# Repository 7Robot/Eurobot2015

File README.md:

# Eurobot2015

     ______  _____      _           _
    |___   /| ___ \    | |         | |
        / / | |_/ /___ | |__   ___ | |_
       / /  |    // _ \|  _ \ / _ \|  _|
      / /   | |\ \ (_) | |_) | (_) | |_
     /_/    |_| \_\___/|____/ \___/ \__|
                              7robot.fr

Gathering repository for the 2015 Robotics French Cup code.

Note : RP7 -> uart2

* Tarantibot

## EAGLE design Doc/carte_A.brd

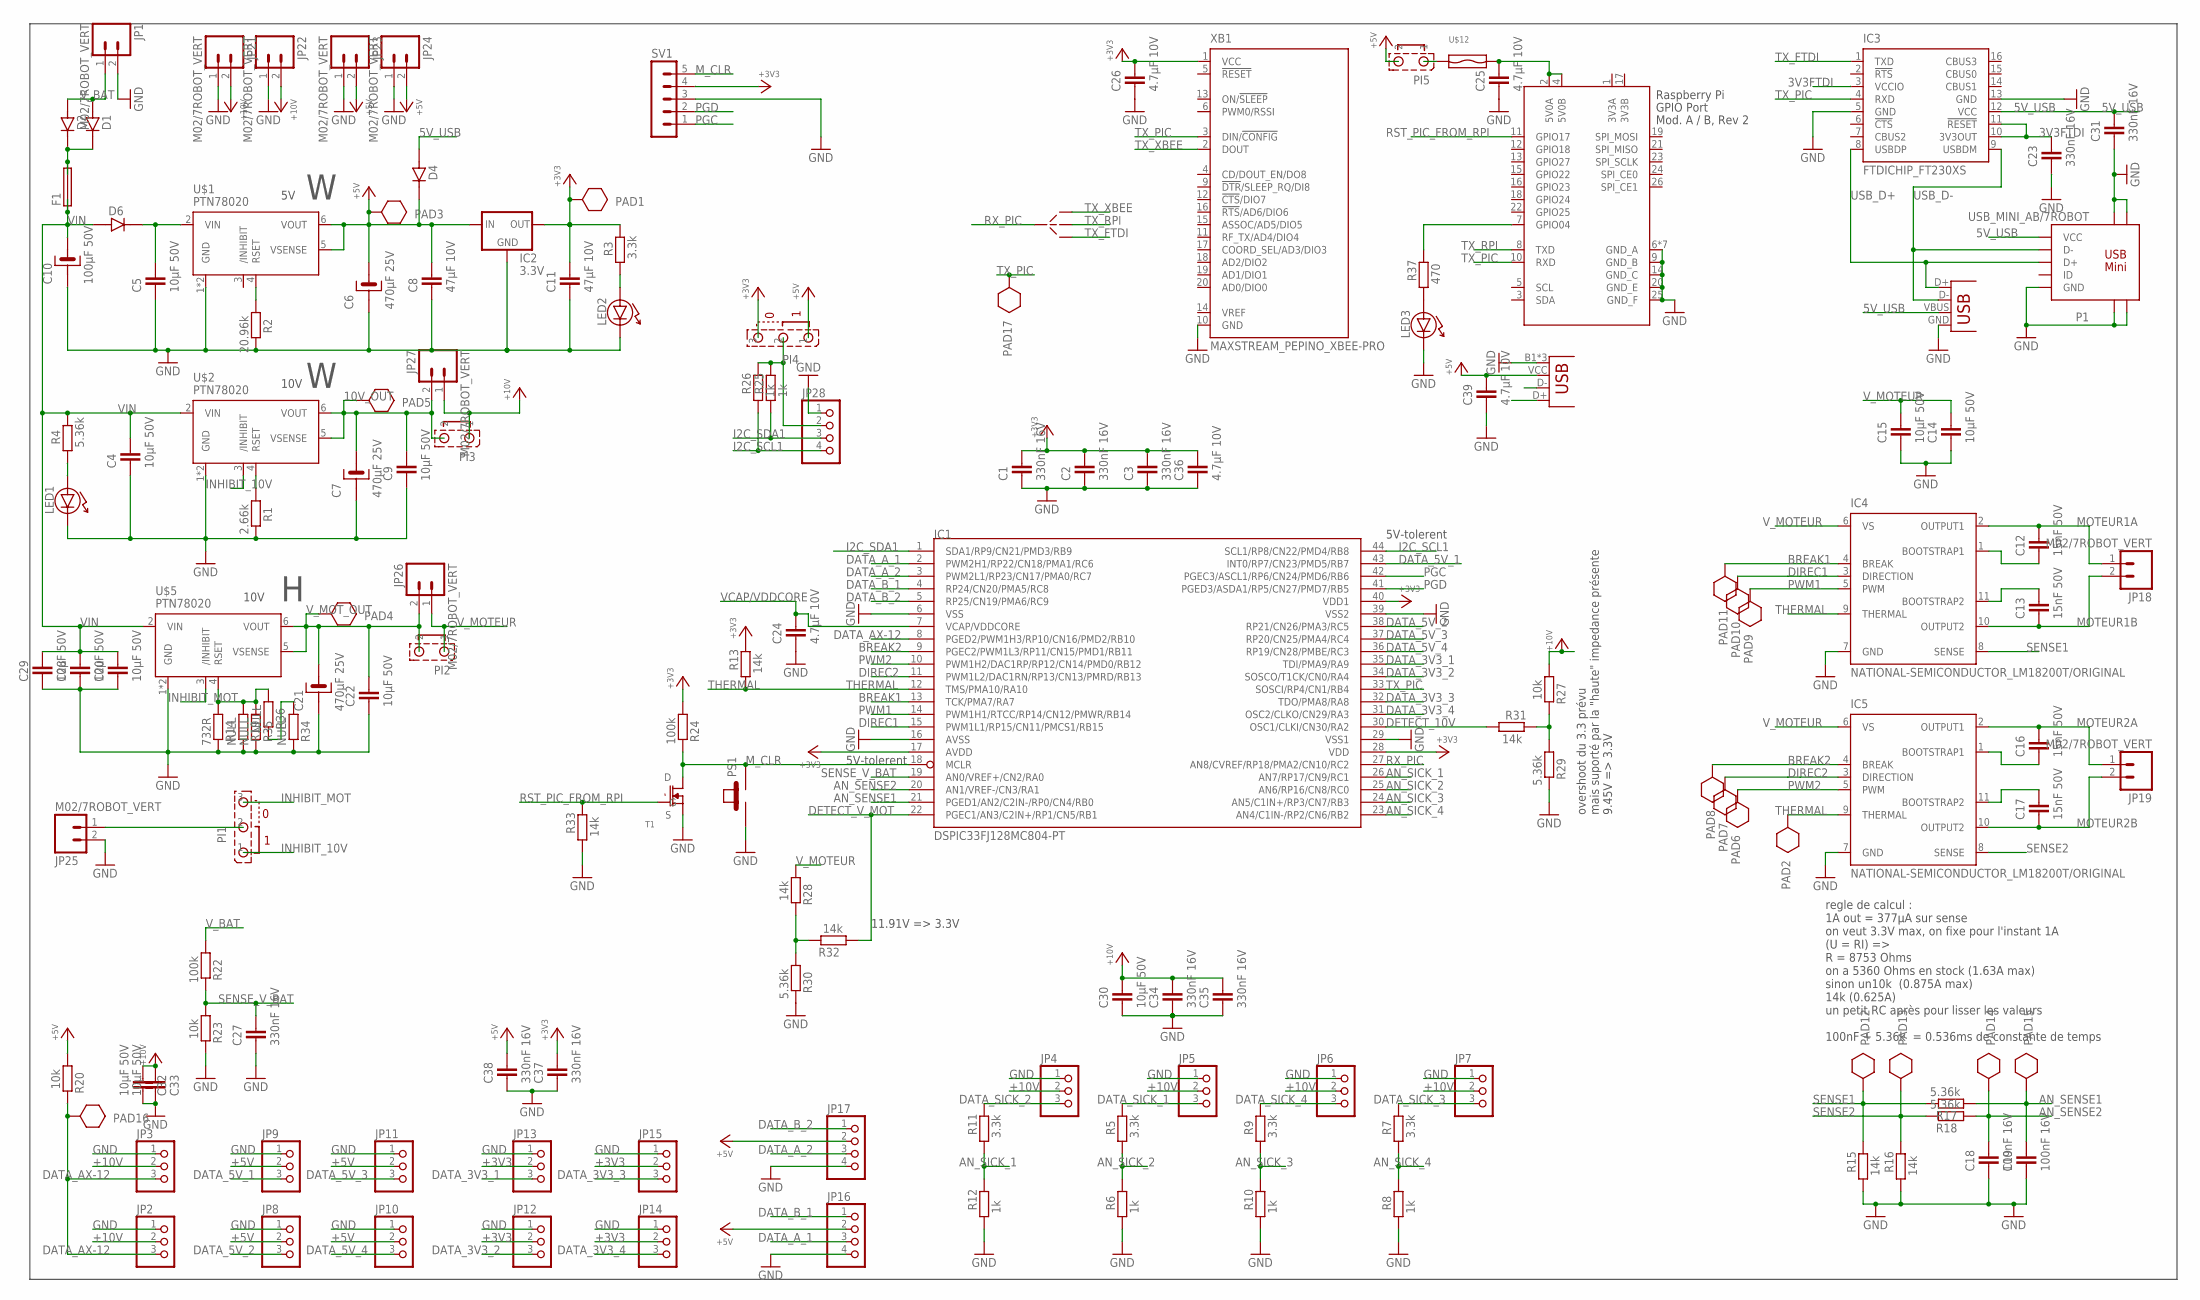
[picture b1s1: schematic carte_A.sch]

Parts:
C1, C2, C3, C23, C27, C31, C34, C35, C37, C38: 330nF 16V; 0805
C4, C5, C9, C14, C15, C20, C22, C28, C29, C30, C32, C33: 10µF 50V; 1206
C6, C7, C21: 470µF 25V; CHIM8P3.5
C8, C11: 47µF 10V; 1210
C10: 100µF 50V; CHIM8P3.5
C12, C13, C16, C17: 15nF 50V; 0805
C18, C19: 100nF 16V; 0805
C24, C25, C26, C36, C39: 4.7µF 10V; 0805
D1, D2, D4, D6: DIODES_DIODE/DO41; DIODES_DO41
F1: PORTE_FUSIBLE; SHK20L
IC1: DSPIC33FJ128MC804-PT; TQFP44
IC2: 3.3V; V-REG_78XXS
IC3: FTDICHIP_FT230XS; FTDICHIP_SSOP16
IC4, IC5: NATIONAL-SEMICONDUCTOR_LM18200T/ORIGINAL; NATIONAL-SEMICONDUCTOR_TO-220-11
JP1, JP18, JP19, JP21, JP22, JP23, JP24, JP25, JP26, JP27: M02/7ROBOT_VERT; CONN_5MM
JP2, JP3, JP4, JP5, JP6, JP7, JP8, JP9, JP10, JP11, JP12, JP13, JP14, JP15: PINHD-1X3; 1X03
JP16, JP17, JP28: PINHD-1X4; 1X04
JP20: USB-B; SPARKFUN-CONNECTORS_USB-B-PTH
JP29: USB/VERT; USB-A-FEMALE_VERTICAL
LED1, LED2: OPTO_OSC_LED/5MM; OPTO_OSC_LED5
LED3: LED/1206; LED1206
P1: USB_MINI_AB/7ROBOT; USB_MINI_AB_7ROBOT
PAD1, PAD3, PAD4, PAD5, PAD17: STRAP_PAD/CMS2; STRAP_PAD_CMS_2
PAD2, PAD6, PAD7, PAD8, PAD9, PAD10, PAD11, PAD12, PAD13, PAD14, PAD15, PAD16: STRAP_PAD/CMS1_5; STRAP_PAD_CMS_1_5
PI1, PI4: STCMS_3/CMS; STCMS_3
PI2, PI3, PI5: STCMS_2
PS1: ELECTROMECA_PEPINO_POUSSOIR/D_MINI; ELECTROMECA_PEPINO_B3F
R1: 2.66k; 0805
R2: 20.96k; 0805
R3, R5, R7, R9, R11: 3.3k; 0805
R4, R17, R18, R29, R30: 5.36k; 0805
R6, R8, R10, R12, R25, R26: 1k; 0805
R13, R15, R16, R28, R31, R32, R33: 14k; 0805
R14: 732R; 0805
R19, R34, R35, R36: NULL; 0805
R20, R23, R27: 10k; 1206
R22, R24: 100k; 1206
R37: 470; 0805
SV1: CON-LSTB_MA05-1
T1: MOS_N/SOT23; SOT23
U$1, U$2, U$5: PTN78020
U$9: STCMS_4
U$12: FUSE_REARMABLE/1206; 1206
X1: RASPI_BOARD_B-#_E6P; RASPI_BOARD_AB-_EDGES_6DRILL_PAD
XB1: MAXSTREAM_PEPINO_XBEE-PRO

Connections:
3V3A: X1.1 (3V3A)
3V3B: X1.17 (3V3B)
3V3FTDI: C23.1, IC3.3 (VCCIO), IC3.10 (3V3OUT), IC3.11 (!RESET)
5V_RPI: C25.1, U$12.2, X1.2 (5V0A), X1.4 (5V0B)
5V_USB: C31.1, D4.A, IC3.12 (VCC), JP20.VBUS, P1.1 (VCC)
10V_OUT: C7.P, C9.1, JP27.2, PAD5.P$1, PI3.2, U$2.5 (VSENSE), U$2.6 (VOUT)
+3V3: C1.1, C2.1, C3.1, C11.1, C26.1, C36.1, C37.1, IC1.17 (AVDD), IC1.28 (VDD), IC1.40 (VDD1), IC2.OUT, JP12.2, JP13.2, JP14.2, JP15.2, PAD1.P$1, PI4.3, R3.2, R13.2, R24.1, SV1.4, XB1.1 (VCC)
+5V: C6.P, C8.1, C38.1, C39.1, D4.K, IC2.IN, JP8.2, JP9.2, JP10.2, JP11.2, JP16.2, JP17.2, JP23.2, JP24.2, JP29.VCC (VBUS), PAD3.P$1, PI4.1, PI5.2, R20.1, U$1.5 (VSENSE), U$1.6 (VOUT)
+10V: C30.1, C32.1, C33.1, C34.1, C35.1, JP2.2, JP3.2, JP4.2, JP5.2, JP6.2, JP7.2, JP21.2, JP22.2, JP27.1, PI3.1, R27.1
AN_SENSE1: C19.1, IC1.21 (PGED1/AN2/C2IN-/RP0/CN4/RB0), PAD15.P$1, R17.1
AN_SENSE2: C18.1, IC1.20 (AN1/VREF-/CN3/RA1), PAD14.P$1, R18.1
AN_SICK_1: IC1.26 (AN7/RP17/CN9/RC1), R11.1, R12.2
AN_SICK_2: IC1.25 (AN6/RP16/CN8/RC0), R5.1, R6.2
AN_SICK_3: IC1.24 (AN5/C1IN+/RP3/CN7/RB3), R9.1, R10.2
AN_SICK_4: IC1.23 (AN4/C1IN-/RP2/CN6/RB2), R7.1, R8.2
BREAK1: IC1.13 (TCK/PMA7/RA7), IC4.4 (BREAK), PAD11.P$1
BREAK2: IC1.9 (PGEC2/PWM1L3/RP11/CN15/PMD1/RB11), IC5.4 (BREAK), PAD8.P$1
DATA_3V3_1: IC1.35 (TDI/PMA9/RA9), JP13.3
DATA_3V3_2: IC1.34 (SOSCO/T1CK/CN0/RA4), JP12.3
DATA_3V3_3: IC1.32 (TDO/PMA8/RA8), JP15.3
DATA_3V3_4: IC1.31 (OSC2/CLKO/CN29/RA3), JP14.3
DATA_5V_1: IC1.43 (INT0/RP7/CN23/PMD5/RB7), JP9.3
DATA_5V_2: IC1.38 (RP21/CN26/PMA3/RC5), JP8.3
DATA_5V_3: IC1.37 (RP20/CN25/PMA4/RC4), JP11.3
DATA_5V_4: IC1.36 (RP19/CN28/PMBE/RC3), JP10.3
DATA_AX-12: IC1.8 (PGED2/PWM1H3/RP10/CN16/PMD2/RB10), JP2.3, JP3.3, PAD16.P$1, R20.2
DATA_A_1: IC1.2 (PWM2H1/RP22/CN18/PMA1/RC6), JP16.3
DATA_A_2: IC1.3 (PWM2L1/RP23/CN17/PMA0/RC7), JP17.3
DATA_B_1: IC1.4 (RP24/CN20/PMA5/RC8), JP16.1
DATA_B_2: IC1.5 (RP25/CN19/PMA6/RC9), JP17.1
DATA_SICK_1: JP5.3, R5.2
DATA_SICK_2: JP4.3, R11.2
DATA_SICK_3: JP7.3, R7.2
DATA_SICK_4: JP6.3, R9.2
DETECT_10V: IC1.30 (OSC1/CLKI/CN30/RA2), R31.1
DETECT_V_MOT: IC1.22 (PGEC1/AN3/C2IN+/RP1/CN5/RB1), R32.1
DIREC1: IC1.15 (PWM1L1/RP15/CN11/PMCS1/RB15), IC4.3 (DIRECTION), PAD10.P$1
DIREC2: IC1.11 (PWM1L2/DAC1RN/RP13/CN13/PMRD/RB13), IC5.3 (DIRECTION), PAD7.P$1
GND: C1.2, C2.2, C3.2, C4.2, C5.2, C6.N, C7.N, C8.2, C9.2, C10.N, C11.2, C14.2, C15.2, C18.2, C19.2, C20.2, C21.N, C22.2, C23.2, C24.2, C25.2, C26.2, C27.2, C28.2, C29.2, C30.2, C31.2, C32.2, C33.2, C34.2, C35.2, C36.2, C37.2, C38.2, C39.2, IC1.6 (VSS), IC1.16 (AVSS), IC1.29 (VSS1), IC1.39 (VSS2), IC2.GND, IC3.5 (GND), IC3.13 (GND), IC4.7 (GND), IC5.7 (GND), JP1.2, JP2.1, JP3.1, JP4.1, JP5.1, JP6.1, JP7.1, JP8.1, JP9.1, JP10.1, JP11.1, JP12.1, JP13.1, JP14.1, JP15.1, JP16.4, JP17.4, JP20.GND, JP21.1, JP22.1, JP23.1, JP24.1, JP25.2, JP28.1, JP29.B1 (GND), JP29.B2 (GND), JP29.GND, LED1.K, LED2.K, LED3.K, P1.5 (GND), P1.SH@1 (PT1), P1.SH@2 (PT2), P1.SH@3 (PT3), P1.SH@4 (PT4), PS1.1, R1.2, R2.2, R6.1, R8.1, R10.1, R12.1, R14.2, R15.1, R16.1, R19.2, R23.2, R29.2, R30.2, R33.1, R34.2, R35.2, SV1.3, T1.2 (S), U$1.1 (GND), U$1.7 (GND), U$2.1 (GND), U$2.7 (GND), U$5.1 (GND), U$5.7 (GND), X1.6 (GND_A), X1.9 (GND_B), X1.14 (GND_C), X1.20 (GND_E), X1.25 (GND_F), X1.41 (GND_A), X1.42 (GND_A), X1.43 (GND_A), X1.44 (GND_A), X1.45 (GND_A), X1.46 (GND_A), XB1.10 (GND)
I2C_SCL1: IC1.44 (SCL1/RP8/CN22/PMD4/RB8), JP28.4, R26.1
I2C_SDA1: IC1.1 (SDA1/RP9/CN21/PMD3/RB9), JP28.3, R25.1
INHIBIT_10V: PI1.1, U$2.3 (/INHIBIT)
INHIBIT_MOT: PI1.3, U$5.3 (/INHIBIT)
MOTEUR1A: C12.1, IC4.2 (OUTPUT1), JP18.1
MOTEUR1B: C13.2, IC4.10 (OUTPUT2), JP18.2
MOTEUR2A: C16.1, IC5.2 (OUTPUT1), JP19.1
MOTEUR2B: C17.2, IC5.10 (OUTPUT2), JP19.2
M_CLR: IC1.18 (MCLR), PS1.4 (2), R24.2, SV1.5, T1.3 (D)
unnamed: R2.1, U$1.4 (RSET)
unnamed: R1.1, U$2.4 (RSET)
unnamed: LED2.A, R3.1
unnamed: LED1.A, R4.1
unnamed: R27.2, R29.1, R31.2
unnamed: R34.1, R36.2
unnamed: C17.1, IC5.11 (BOOTSTRAP2)
unnamed: R28.2, R30.1, R32.2
unnamed: D1.K, D2.K, F1.2A, F1.2B
unnamed: C5.1, D6.K, U$1.2 (VIN)
unnamed: C12.2, IC4.1 (BOOTSTRAP1)
unnamed: C13.1, IC4.11 (BOOTSTRAP2)
unnamed: PI5.1, U$12.1
unnamed: R14.1, R19.1, R35.1, R36.1, U$5.4 (RSET)
unnamed: LED3.A, R37.1
unnamed: C16.2, IC5.1 (BOOTSTRAP1)
unnamed: R37.2, X1.7 (GPIO04)
unnamed: JP25.1, PI1.2
PGC: IC1.42 (PGEC3/ASCL1/RP6/CN24/PMD6/RB6), SV1.1
PGD: IC1.41 (PGED3/ASDA1/RP5/CN27/PMD7/RB5), SV1.2
PWM1: IC1.14 (PWM1H1/RTCC/RP14/CN12/PMWR/RB14), IC4.5 (PWM), PAD9.P$1
PWM2: IC1.10 (PWM1H2/DAC1RP/RP12/CN14/PMD0/RB12), IC5.5 (PWM), PAD6.P$1
RST_PIC_FROM_RPI: R33.2, T1.1 (G), X1.11 (GPIO17)
RX_PIC: IC1.27 (AN8/CVREF/RP18/PMA2/CN10/RC2), U$9.C
SENSE1: IC4.8 (SENSE), PAD12.P$1, R15.2, R17.2
SENSE2: IC5.8 (SENSE), PAD13.P$1, R16.2, R18.2
SENSE_V_BAT: C27.1, IC1.19 (AN0/VREF+/CN2/RA0), R22.2, R23.1
THERMAL: IC1.12 (TMS/PMA10/RA10), IC4.9 (THERMAL), IC5.9 (THERMAL), PAD2.P$1, R13.1
TX_FTDI: IC3.1 (TXD), U$9.3
TX_PIC: IC1.33 (SOSCI/RP4/CN1/RB4), IC3.4 (RXD), PAD17.P$1, X1.10 (RXD), XB1.3 (DIN/!CONFIG)
TX_RPI: U$9.2, X1.8 (TXD)
TX_XBEE: U$9.1, XB1.2 (DOUT)
USB_D+: IC3.8 (USBDP), JP20.D+, P1.3 (D+)
USB_D-: IC3.9 (USBDM), JP20.D-, P1.2 (D-)
VCAP/VDDCORE: C24.1, IC1.7 (VCAP/VDDCORE)
VIN: C4.1, C10.P, C20.1, C28.1, C29.1, D6.A, F1.1A, F1.1B, R4.2, U$2.2 (VIN), U$5.2 (VIN)
V_BAT: D1.A, D2.A, JP1.1, R22.1
V_I2C: JP28.2, PI4.2, R25.2, R26.2
V_MOTEUR: C14.1, C15.1, IC4.6 (VS), IC5.6 (VS), JP26.1, PI2.1, R28.1
V_MOT_OUT: C21.P, C22.1, JP26.2, PAD4.P$1, PI2.2, U$5.5 (VSENSE), U$5.6 (VOUT)

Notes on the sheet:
10V
5V-tolerent
regle de calcul : 1A out = 377µA sur sense on veut 3.3V max, on fixe pour l'instant 1A (U = RI) => R = 8753 Ohms on a 5360 Ohms en stock (1.63A max) sinon un10k (0.875A max) 14k (0.625A) un petit RC après pour lisser les valeurs 100nF + 5.36k = 0.536ms de constante de temps
overshoot du 3.3 prévu mais suporté par la "haute" impedance présente 9.45V => 3.3V
11.91V => 3.3V

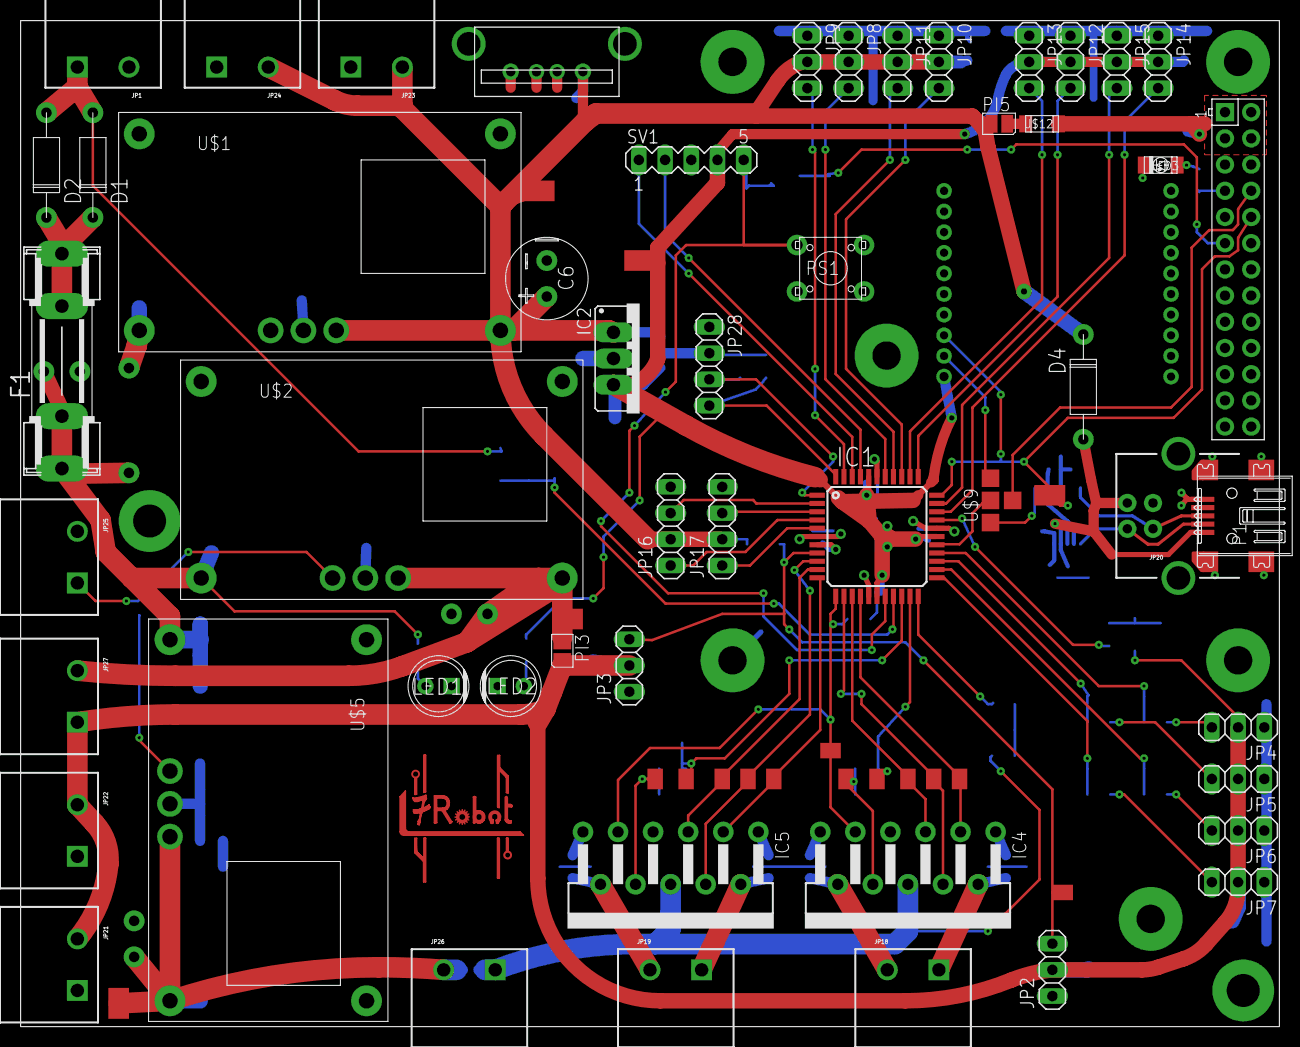
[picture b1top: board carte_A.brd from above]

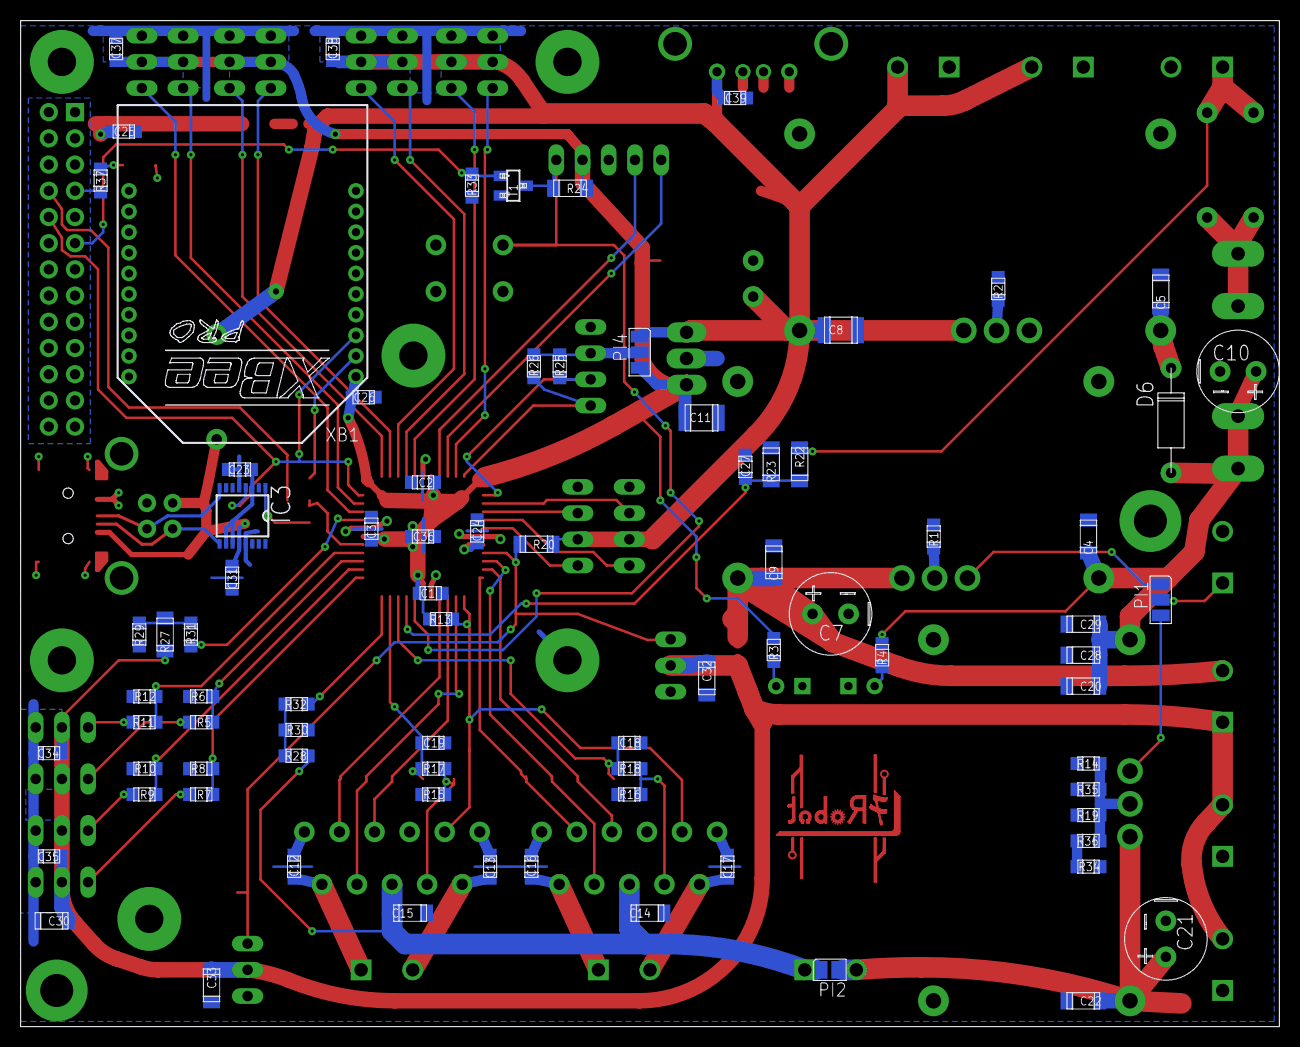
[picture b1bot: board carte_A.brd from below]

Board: 8 copper layers, 122.0 x 97.5 mm, 151 parts (81 on the bottom side), 86 nets.

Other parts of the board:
U$3: 7ROBOT

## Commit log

2015-03-01 First commit for moves code
2015-03-13 Initialisation du dépot de l'asserv
2015-03-13 ajout du dépot de l'asserv
2015-03-14 ajout de fichier et configuration du dépot 2015
2015-03-14 Ajout de la lib_asserv Ajout des fichiers de configuration moteurs motor.c : motor.h Ajout des fichiers user.c :: user.h
2015-03-14 ajout du fichiers d'interruption ajout d'un dossier de doc
2015-03-16 ajout de pragma pour gérer le debug et AX12.c et AX12.h
2015-03-17 ajout de l'ascii art 7robot
2015-03-21 UART AX12 configuré
2015-03-21 Les queis fonctionnent ;)
2015-03-21 pwm fonctionnel
2015-03-21 avancé du code pic, les moteurs fonctionnent + ajout d'une feature de pépino
2015-03-25 ajout des actions des ax12
2015-03-26 Rangement
2015-03-26 joli logo
2015-03-28 réglage des moteurs: qei respectifs, résolution du problème des qei "fous" ajout d'une lib pour faire du serial en cpp
2015-03-28 ajout de l'uart1 du pic
2015-04-01 réglage de l'asserv , asserv en vitesse semble opérationnel
2015-04-01 ajout du code de fabien, fonctionne :) remarque les delais sont un peu long ... à ameliorer , problème trouvé dans le sens des moteurs, à régler pour le prochain commit
2015-04-08 correction d'une erreur static float -> static volatile int
2015-04-08 ajout d'un projet Bottox
2015-04-13 ajout de doc
2015-04-13 ajout asserv tarantibot
2015-04-14 ajout image Tarantibot
2015-04-14 actualisation image Hitch
2015-04-17 ajout simulateur d'asserv d'Alex
2015-04-22 ajout pathfinding de tristan
2015-04-26 manquait #include <cstdlib>
2015-04-26 ajout readme pathfinding
2015-04-27 test change notification pins capteurs moteurs
2015-04-27 ajout doc XC16
2015-04-27 interruption sur changements d'état capteurs moteurs fonctionnelles avec debugg uart
2015-04-27 ajout du git ignore
2015-04-27 Fonction d'envoi uart pour hitchbot
2015-04-27 ajout d'un bout de truc qui fait semblant de bouger le robot
2015-04-28 test asserv ca marche pas
2015-04-28 Ajout fichiers projet Sublime Text (useless stuff)
2015-04-28 asserv d'alex
2015-04-28 commentaire de la laisse
2015-04-28 nmbre de ticks par metre tarant
2015-04-28 Réception d'une commande en UART depuis la Pi et stockage dans un tableau global
2015-04-28 ajout des sicks -> pas configurés
2015-04-28 commit pour tristan
2015-04-29 makefile pb solved
2015-04-29 ca a l'air de remarcher...
2015-04-29 Actions AX12 en cours
2015-04-29 ajout des fichiers de Léo
2015-04-29 Ignore MPLABX files
2015-04-29 pull pour léo
2015-04-29 *configuration des sicks *ax12 merdique
2015-04-29 Ajout Commande en position MOVE dans communication
2015-04-29 Erreur de merge
2015-04-29 Essai d'ignorer les fichiers config MPLABX
2015-04-29 Problème de merge encore, ça compile maintenant
2015-04-29 Encore un essai pour ignorer cette config MPLABX
2015-04-29 correction include
2015-04-29 backup de l'asserv
2015-04-29 stratégie de l'echec - refonte asserv tarantibot
2015-04-29 ajout oublie rx uart2
2015-04-29 Fix pour pouvoir lancer plusieurs commandes
2015-04-29 AX_12_delays_good
2015-04-29 asserv maison
2015-04-29 Nothing
2015-04-30 PID propre Tarantibot
2015-05-02 petites corrections asserv tarant.
2015-05-02 l'asserv semble fonctionner :)
2015-05-02 Ajout de sick.h et sick.c
2015-05-02 action ax12 tarantibot
2015-05-02 correction asserv + communication
2015-05-03 Centralisation des includes pour un truc plus propre
2015-05-03 Correction de l'ordre des includes
2015-05-03 Fix pb des dossiers MPLab en conflit, désormais ignorés
2015-05-03 merge
2015-05-03 Piti correctif Ax_12
2015-05-03 Fix include dans l'asserv
2015-05-03 correction bug asserve tarantibot
2015-05-03 Test des déplacements
2015-05-03 Backup
2015-05-03 asserv tarant
2015-05-03 Actions qui marchent
2015-05-03 réparation des conneries de celui qui a supprimé plein de fichiers de tarantibot..
2015-05-03 réparélébétise
2015-05-03 actions ax12 Tarantibot
2015-05-03 MERGEE
2015-05-03 WOuhouu robot qui roule avec une asserv approcimative et des ax12 qui dépotent
2015-05-04 tunage release _ DENIS
2015-05-04 Nouveau Done, action INIT et fix accélération
2015-05-04 ajout du detecteur de spot
2015-05-04 ajout début de code pour les sicks pour desactiver les printf : commenter la ligne #define DEBUG_SICK dans user.h
2015-05-04 ajout de bordel
2015-05-04 IL MONTE LES MAAARCHES
2015-05-04 Ca monte un peu, on attend (déployage tapis) et on finit de monter
2015-05-05 toutes petites modifs sur les sicks + tentative d'amélioration gitignore
2015-05-05 NE PAS IGNORER LES DOSSIERS DU PROJET (ex nbproject) SINON CA FOUT LA MERDE
2015-05-05 on répare les betises blabalbal
2015-05-05 moyenne tournante pour les sicks déplacement du define de débug
2015-05-05 les .elf et .hex, ils sont modifiés à chaque compil, mais n'ont pas besoin d'êtres comités, déjà mis en gitignore
2015-05-05 Tuning des ax12 de Tarantibot
2015-05-05 ajout de Get_Sick et Get_Sick_Sector besoin de stdint.h de partout du coup
2015-05-05 Bouton couleur fonctionnel
2015-05-06 modif gitignore pour enlever la modif de date de derniere compil...
2015-05-06 "detection" de sick mal branché...
2015-05-06 prout
2015-05-06 ajustement coef asserv (fonctionnel)
2015-05-06 ajout de la fonction angle dans la com
2015-05-06 ajout de la com sick
2015-05-06 ajustement angles ax12 tarantibot
2015-05-06 detail + comment sick + comment debug -> Seuil sick non fonctionnel
2015-05-06 commit d'un code pas fonctionnel pour pépino
2015-05-06 ajout d'une fonction close_claw() qui permet la fermeture à la volée des pinces, ne renvoit pas de "done"
2015-05-06 tableau des seuils pour sicks mal initialisé
2015-05-06 ajout release+detect sick possibilité de demander l'état du sick : $SIK?,numerodusick;
2015-05-06 ajout du code de léo, CN / interuption / laisse / pas drole
2015-05-06 avancement des sicks ajout qq bidules dans communication.c (des break, hein Mr Proux)
2015-05-06 encores modifs debug sicks + communication
2015-05-07 Ajout de la gestion du bouton d'équipe sur Alfred
2015-05-07 Correction détection erreur Asserv infondée
2015-05-07 ajout d'un bout d'ia, qui permet de faire l'homologation, gestion des sicks /!\ problème sur l'ia
2015-05-08 gestion ultrason ! $DULS; = Detect ultrason $RULS; = release ultrasons
2015-05-08 renvoi de la pin team vers le connecteur 3V
2015-05-08 Revert "ajout d'un bout d'ia, qui permet de faire l'homologation,"
    This reverts commit ff687adad205c9326dc526cd8623176870c5a778.
2015-05-08 oups, les fichiers ^^
2015-05-08 ajout de fonction open_clap / close_clap
2015-05-08 ajout de la com open_clap / close_clap
2015-05-08 ajout de sendDone dans la fonciton de fermeture des claps
2015-05-08 ajout VBat
2015-05-08 modif Vbat
2015-05-08 ajout de fonction de la fonciton ax12 pour attraper le popcorn
2015-05-08 tunage AX12 , debug de la com ax12 xD
2015-05-08 modif mais l'asserv a des comportements étranges
2015-05-09 configuration de l'asserv
2015-05-09 modif de interrupt CN, histoire que ça se passe mieux...
2015-05-09 passage old laisse en static (sorry)
2015-05-09 ajout de la fonctionnalité ultra son sur tarantibot... pas testé
2015-05-09 Ajout de ENSI,0/1 et ENUS,0/1 pour desactiver le motion free des sicks et de l'ultrason
2015-05-09 ajustement coef
2015-05-09 comit de code pour matthieu , modif dans l'asserv des lignes 238 (d/2) de asserv.c
2015-05-09 tarantibot sans asserv, yolo
2015-05-09 maj coeff asserv fonctionne #pasmal
2015-05-09 ajout de correction AX12 / vitesse torque global + modif popcorn
2015-05-09 modif AX12 popcorn ok
2015-05-09 modif ax12
2015-05-09 ajout ultrason tarantibot
2015-05-09 modif init ax12
2015-05-10 close_claws open_claws synchrone
2015-05-10 petite modif de pépino sur la laisse
2015-05-10 petite extension de range sicks
2015-05-10 Ajout coeffs pour l'homologation
2015-05-10 La pince qui se ferme en premier dépend de la position
2015-05-10 Coeff pour la battle en place
2015-05-10 Optimisation tempos des AX12
2015-05-10 ajout attente réponse AX12, pour l'instant pas testé, et pas intégré + doc AX12 dans dossier DOC
2015-05-10 make-files qui font chier....
2015-05-10 test de la réponse AX12 sur open et close popcorn
2015-05-10 ajout d'un buffer pour la réalisation des actions AX12...
2015-05-10 "typo"
2015-05-11 Un peu trop optimiste sur les actions des AX12
2015-05-11 Ajout de l'IA python à mettre sur la Pi
2015-05-11 Remove des DONE dans certaines actions AX12
2015-05-11 ajout de la fonction close_tub
2015-05-11 ajout possibilité double commande...
2015-05-11 Le sick obstrué par tarantibot au départ n'est pas génant
2015-05-11 modifs de ce qu'il faut pour avoir les réponses des AX12, c'est testé, je vais tenter de l'intégrer plus d'ici ce soir ou demain matin
2015-05-12 ajustements tarantibot
2015-05-12 modif commande AX12 : regarde la réponse à chaque fois, et retente 10 fois si réponse mauvaise, fail après 10 tentatives...
2015-05-12 FOR ALEX /!\ préparation du code pour tester les AX12 à full speed
2015-05-12 VMAX modifiable par la PI VMAX,1.2; => vitesse à 1.2m/s en max
2015-05-12 Désactivation des sicks un par un : ENSI,F pour tous les activer ENSI,0 pour tous les desactiver ENSI,1 pour le 0 seulement ENSI,5 pour activer le 0 et le 2
2015-05-13 remise au propre de la tentative AX12 1Meg, et ajout du compteur 90 sec qui bousille tout
2015-05-14 ajout de clap droit et gauche : CLLO et CLLC pour le LEFT CLRO et CLRC pour le RIGHT modif de seuil pour les sicks en meme temps
2015-05-14 DESACTIVER CA OBLIGATOIREMENT POUR MATCH
2015-05-14 modif coef asserv minimaux plateau CDF
2015-05-14 petit truc, esperons que ça pete pas tout
2015-05-14 Sur la demande de tristan schultz, ajout de nouvelle fonction ax12 qui distinguent droite/gauche
2015-05-14 butage pour de bon de sick3...
2015-05-14 correction valeur actions ax12 popcorn
2015-05-14 inversion sens pinces pour dernier spot
2015-05-14 coef ax12
2015-05-14 remise sick 3
2015-05-14 add fonction previent fin des 90 secs
2015-05-14 tune coef
2015-05-14 modif gestion 90secs
2015-05-14 tune avancé
2015-05-14 un truc c'est passé dans comm.c
2015-05-14 patch
2015-05-14 patch 2
2015-05-14 patch3
2015-05-14 patch 4
2015-05-14 code du premier match
2015-05-14 Ajout victory_dance pour Hitchbot et Tarantibot
2015-05-14 OMG what happen to the asserv Oo => back up -> fonctionnel (apparemment )
2015-05-14 On a tout refé !
2015-05-14 modification de RELE
2015-05-14 ajout de GetAX_Pos.... pas testé renvoi -1 si réponse FAILED
2015-05-14 qqelques modifs pour reprendre en compte le bouton mort et ajout de remontage de pince pour chope_spot
2015-05-15 petites modifs ax12 (charge spot et release)
2015-05-15 ajout get AX position
2015-05-18 code final de Tarantibot
2015-05-27 copie de l'asserv dans un coin, spécification de la nouvelle
2015-09-14 Tarantibot_CLIP
